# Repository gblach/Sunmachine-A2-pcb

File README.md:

# Sunmachine-A2-pcb
The driver for WS2812, SK6812 or similar LED strips controlled via Bluetooth LE. It supports both RGB and WWA LEDs.
This driver uses motion and light sensors, so in automatic mode it can turn on the light when it detects someone's presence in the dark.
The PCB is designed for the [Hammond 1551V3](https://www.hammfg.com/electronics/small-case/plastic/1551v) enclosure, so it can be hung on a wall or ceiling.
The firmware for the board is available in [Sunmachine-A2-fw](https://github.com/gblach/Sunmachine-A2-fw) repo
and the mobile app to control the board is available in [Sunmachine-app](https://github.com/gblach/Sunmachine-app) repo.

## Key components
- [Minew MS50SFA2](https://www.minew.com/product/nrf52832-ms50sfa2/) module with Nordic nRF52832 processor.
- RCWL-0516 microwave motion sensor.
- 5626 photodiode (5526 should work too).
- SN74LV1T34DBV level shifter.
- LM1117-3.3 voltage regulator.

## Connectors
- 2-pin ARK connector - for a power supply (5V).
- 3-pin ARK connector - for a LED strip (max. 6A).
- Tag-Connect 2050 - for a programmer.

## Production files
- [Gerber file](Sunmachine-A2.zip)
- [Bill of materials](Sunmachine-A2.csv)

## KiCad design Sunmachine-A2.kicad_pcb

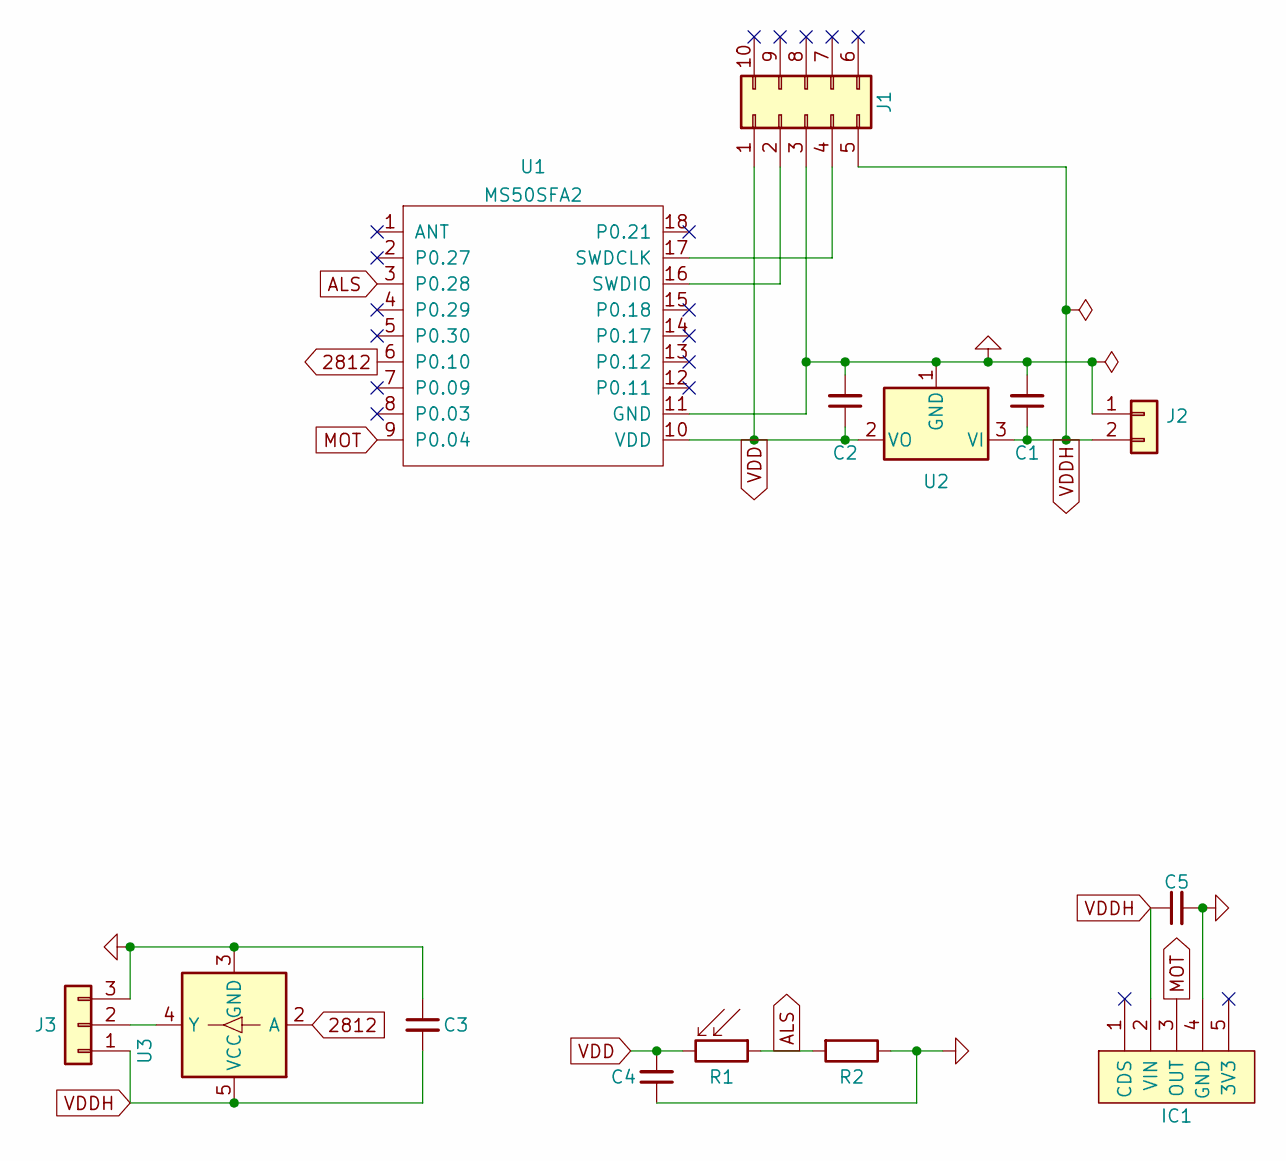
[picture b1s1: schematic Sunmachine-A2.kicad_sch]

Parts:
C1, C2, C3, C4, C5: 10uF; C_0805_2012Metric_Pad1.18x1.45mm_HandSolder; LCSC C15850
IC1: RCWL-0516; RCWL-0516-3
J1: Conn_02x05_Counter_Clockwise; Tag-Connect_TC2050-IDC-NL_2x05_P1.27mm_Vertical_with_bottom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
J2: Conn_01x02; TerminalBlock_4Ucon_1x02_P3.50mm_Horizontal
J3: Conn_01x03; TerminalBlock_4Ucon_1x03_P3.50mm_Horizontal
R1: 5626; R_LDR_5.1x4.3mm_P3.4mm_Vertical
R2: 10k; R_1206_3216Metric_Pad1.30x1.75mm_HandSolder; LCSC C17902
U1: MS50SFA2
U2: LM1117-3.3; SOT-223-3_TabPin2; LCSC C6186
U3: SN74LV1T34DBV; SOT-23-5_HandSoldering; LCSC C100024

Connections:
2812: U1.6 (P0.10), U3.2 (A)
ALS: R1.1, R2.2, U1.3 (P0.28)
GND: C1.2, C2.2, C3.1, C4.1, C5.2, IC1.4 (GND), J1.3, J2.1, J3.3, R2.1, U1.11 (GND), U2.1 (GND), U3.3 (GND)
MOT: IC1.3 (OUT), U1.9 (P0.04)
unnamed: J1.2, U1.16 (SWDIO)
unnamed: J1.4, U1.17 (SWDCLK)
unnamed: J3.2, U3.4 (Y)
VDD: C2.1, C4.2, J1.1, R1.2, U1.10 (VDD), U2.2 (VO)
VDDH: C1.1, C3.2, C5.1, IC1.2 (VIN), J1.5, J2.2, J3.1, U2.3 (VI), U3.5 (VCC)

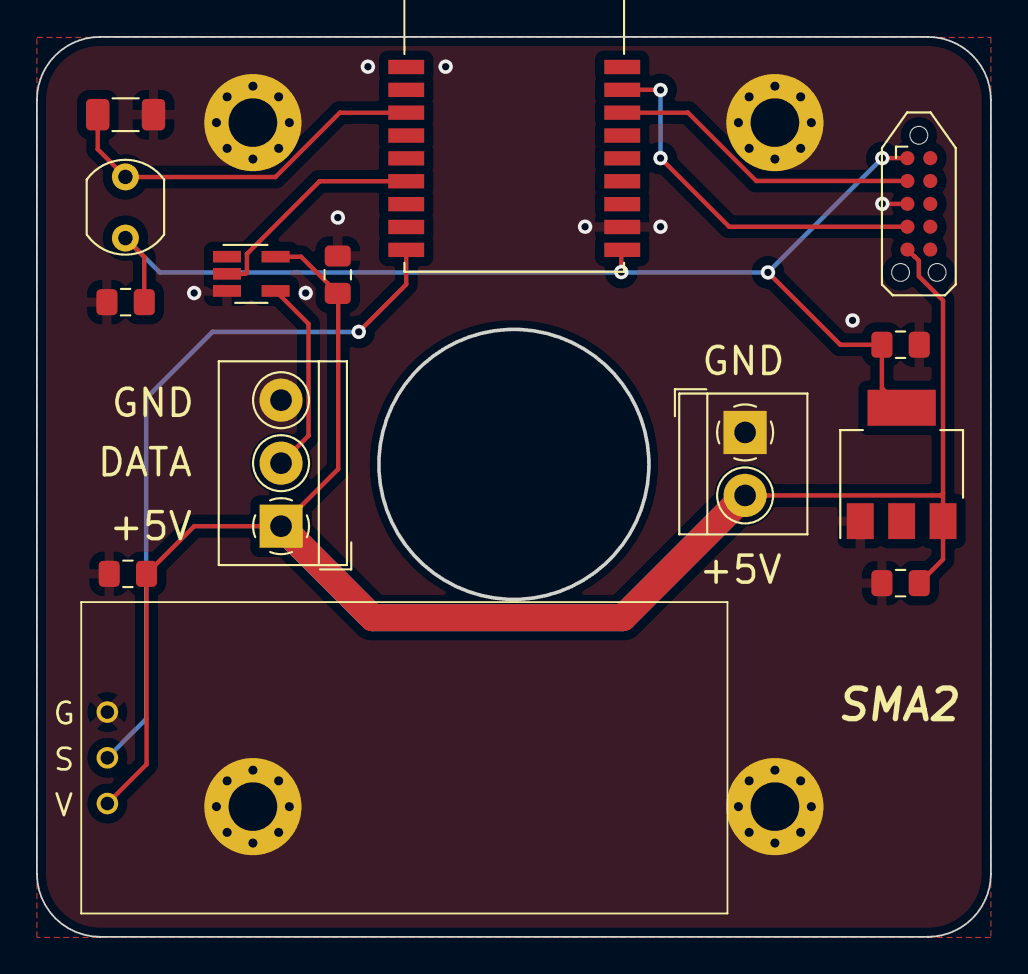
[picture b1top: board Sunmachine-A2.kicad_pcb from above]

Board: 2 copper layers, 52.9 x 49.9 mm, 14 parts (0 on the bottom side), 9 nets.

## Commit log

2022-01-18 Initial import
2022-01-30 Add links to the firmware and the mobile app
